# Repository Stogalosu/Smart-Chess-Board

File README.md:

# Smart Chess Board

## What?
A smart chess board that connects to your phone and automatically makes the moves you and your opponent make on the screen. It can even play against you! It works by moving a magnet under the board, thus also moving the pieces which will have magnets in them.

## Why?
Because I had this idea in the back if my head for a long time and I thought this was the perfect time. Also, I wanted a challenge, something new.

## How do I use it?
Well, I haven't thought it through, but my idea is to also make an Android app that connects through Bluetooth with the board so you can visualise the moves there, as well as make new ones. I also hope to allow players to make their own moves on the board using the Hall sensors that are in the board.

## Firmware
There is no firmware... yet. I've just finished assembling the board and will start working on the firmware soon. 

## Disclosure
This project has already been submitted to Blueprint a few months ago. In the meantime, I've made some small additions and adjustments that I've recorded using Lapse. These include:
- Adding pin holes on the x-axis idlers for the pulleys and then increasing their tolerances.
- Modifying X-carriage to avoid interference of belts with other moving pieces.
- Adding snap fit to every chess piece.
- Adding fillets to board edges.
- Reworking screw holes on the sides of the board.
- Strengthening the bottom of the board.
- Adjusting eject mechanism angle.
- Adjusting position of holes for Raspberry Pi.
- Adding holes in the bottom of the board for belt tensioning screws.
- Adding spaces for pin solders on the back of the PCB.
- Widening nut spaces in all pieces.
- Fixing nut holes for the motor holes; the nut was too close to the motor.
- Fixing small problems before shipping.

## Assembly
Print all pieces. Make sure to follow the color scheme of a real chess board and keep track of which piece is which, as some of the screw holes won't align if their positions are wrong. Slide together the 4 pieces that make up the bottom of the board while inserting the y-axis rods, the x-axis idlers and the x-axis guiderail. Screw in the motor holders and the motors. Cut your belt into 2 pieces. Slide them into the x-axis carriage and fit the belts on the pulleys as described in the following image. Screw in the x-axis carriage. Attach the servomotor.

Solder the pieces onto the PCB and solder them together by connecting the pins. Connect the botton pieces of the play surface with the little pins. Fit the PCBs into it, then screw in each wall piece while keeping track of its position. Connect the motor cables and the Raspberry Pi.

At the end, cover the bottom with the play surface and screw in all the screws. Done!

## Images
Build:

3D Render:

PCB that has the Raspberry Pi on it:

The other PCB, which will be used 3 times to form a grid:

Wiring diagrams for the special PCB:

Wiring diagram for tileable PCB:

## BOM table
|Name                          |Price/unit|Amount|Shipping|Product Cost|Notes           |Link                                                                                                        |
|------------------------------|----------|------|--------|------------|----------------|------------------------------------------------------------------------------------------------------------|
|X-axis guiderail              |$13,37    |1     |$0,00   |$13,37      |MGN9H, 350mm    |https://www.aliexpress.com/item/1005002516956172.html                                                       |
|Y-axis Steel Rod              |$2,21     |2     |$1,12   |$5,54       |6mm, 350mm      |https://www.aliexpress.com/item/1005007648646117.html                                                       |
|Y-axis Linear Bearing         |$1,26     |2     |$0,00   |$2,52       |LM6UU           |https://www.optimusdigital.ro/ro/mecanica-rulmenti/3812-rulment-liniar-lm6uu.html                           |
|Stepper Motor                 |$3,88     |2     |$0,00   |$7,76       |                |https://www.optimusdigital.ro/ro/motoare-motoare-pas-cu-pas/101-driver-uln2003-motor-pas-cu-pas-de-5-v-.html|
|Servomotor                    |$3,20     |1     |$0,00   |$3,20       |                |https://www.optimusdigital.ro/ro/motoare-servomotoare/26-micro-servomotor-sg90.html                         |
|Neodymium Magnet 6x3mm        |$2,26     |1     |$0,00   |$2,26       |                |https://www.emag.ro/magnet-neodim-disc-6mm-x-3mm-00004824/pd/DZW0Y6BBM/                                     |
|Neodymium Magnet 10x3mm       |$6,97     |2     |$6,48   |$20,42      |100pcs          |https://www.aliexpress.com/item/1005010439392352.html                                                       |
|GT2 Belt                      |$2,31     |1     |$1,82   |$4,13       |                |https://www.robofun.ro/3d-printer-cnc/curea-gt2-la-metru-liniar.html                                        |
|M3x6 Headless Screws          |$0,08     |10    |$0,00   |$0,77       |                |https://www.optimusdigital.ro/ro/mecanica-suruburi-si-piulite/5785-m3x6-mm-urub-de-fixare-cu-cap-plat.html  |
|M3x6 Screws                   |$0,02     |100   |$6,00   |$8,00       |Minimum quantity|https://www.tme.eu/ro/details/m3x6_d912-a2/suruburi-cu-piulita/kraftberg/                                   |
|M3x10 Screws                  |$0,03     |100   |$0,00   |$3,20       |Minimum quantity|https://www.tme.eu/ro/details/b3x10_bn3/suruburi-cu-piulita/bossard/1003771/                                |
|Steel Pins 2.5x10mm           |$4,60     |1     |$0,00   |$4,60       |50pcs           |https://www.aliexpress.com/item/1005003326358562.html                                                       |
|Steel Pins 4x30mm             |$5,04     |1     |$0,00   |$5,04       |20pcs           |https://www.aliexpress.com/item/1005003326358562.html                                                       |
|GT2 Timing Pulleys 5pcs       |$5,53     |1     |$2,99   |$8,52       |20T W6 B5       |https://www.aliexpress.com/item/1005001933418605.html                                                       |
|GT2 Idler Timing Pulleys 12pcs|$9,28     |2     |$2,99   |$21,55      |20T W6 B4       |https://www.aliexpress.com/item/1005007557987612.html                                                       |
|Hall Sensors                  |$0,41     |65    |$0,00   |$26,65      |                |https://www.tme.eu/ro/details/ss30at/senzori-hall/honeywell/                                                |
|I2C I/O expander              |$1,66     |1     |$0,00   |$1,66       |                |https://www.tme.eu/ro/en/details/tca9555pwr/interfaces-others-integrated-circuits/texas-instruments/        |
|I2C Driver                    |$1,69     |1     |$0,00   |$1,69       |                |https://www.tme.eu/ro/en/details/tbd62083afwg/drivers-integrated-circuits/toshiba/                          |
|Resistor network              |$0,30     |1     |$0,00   |$0,30       |                |https://www.tme.eu/ro/en/details/4609x-101-103lf/resistor-networks/bourns/                                  |
|Bus transciever               |$0,80     |1     |$0,00   |$0,80       |                |https://www.tme.eu/ro/en/details/sn74hct245dwr/latches/texas-instruments/                                   |
|Resistors                     |$0,03     |5     |$0,00   |$0,13       |                |https://www.tme.eu/ro/details/rc1206fr-072k7/rezistente-smd/yageo/rc1206fr-072k7l/                          |
|Inductors                     |$0,41     |4     |$0,00   |$1,64       |                |https://www.tme.eu/ro/details/b82422h1103k000/inductoare/epcos-tdk/                                         |
|Polarized Capacitors          |$0,70     |4     |$0,00   |$2,80       |                |https://www.tme.eu/ro/details/tajc107k010r/condensatoare-cu-tantal-smd/kyocera-avx/tajc107k010rnj/          |
|Capacitors                    |$0,17     |3     |$0,00   |$0,51       |                |https://www.tme.eu/ro/details/cl31b104kbcnnnd/condensatoare-mlcc-smd/samsung/                               |
|40 pin Connector Female       |$0,46     |1     |$0,00   |$0,46       |                |https://www.tme.eu/ro/details/zl262-40dg/pini-cu-benzi-si-soclu/connfly/ds1023-2-20s21/                     |
|40 pin Connector Male         |$4,51     |1     |$0,00   |$4,51       |                |https://www.tme.eu/ro/details/zl2038-40/pini-cu-benzi-si-soclu/ninigi/                                      |
|7 pin Connector Female        |$0,08     |10    |$0,00   |$0,81       |Minimum quantity|https://www.tme.eu/ro/details/zl262-7sg/pini-cu-benzi-si-soclu/connfly/ds1023-1-7s21/                       |
|4 pin Connector Female        |$0,08     |10    |$0,00   |$0,78       |Minimum quantity|https://www.tme.eu/ro/details/zl262-4sg/pini-cu-benzi-si-soclu/connfly/ds1023-1-4s21/                       |
|3 pin Connector Male          |$0,17     |1     |$0,00   |$0,17       |                |https://www.tme.eu/ro/details/tsw-103-07-l-s/pini-cu-benzi-si-soclu/samtec/                                 |
|PCBs                          |$29,40    |1     |$22,59  |$51,99      |                |                                                                                                            |
|Total Cost                    |          |      |$43,99  |$205,78     |                |                                                                                                            |

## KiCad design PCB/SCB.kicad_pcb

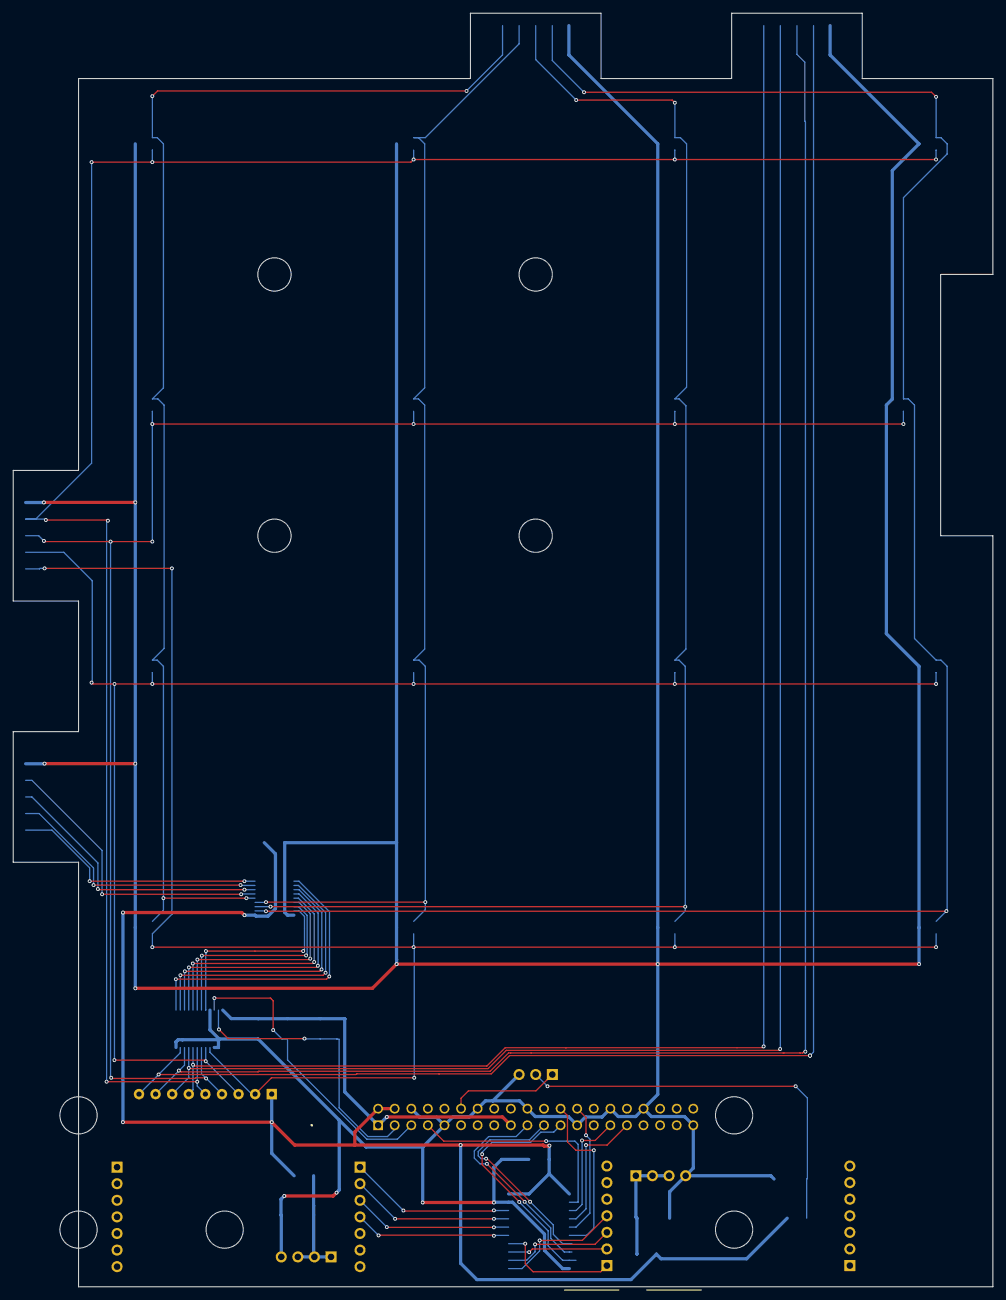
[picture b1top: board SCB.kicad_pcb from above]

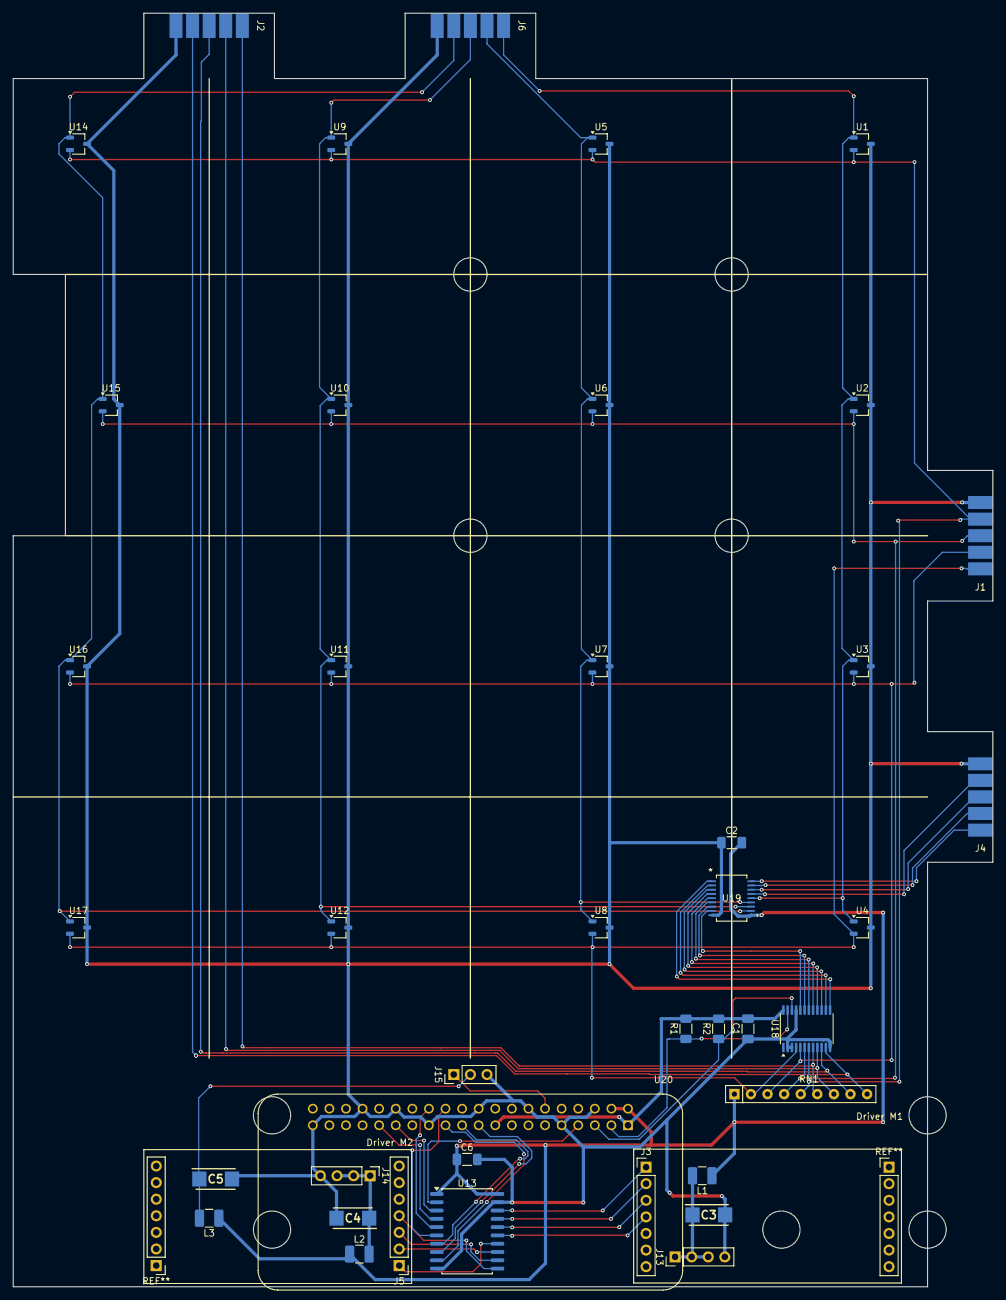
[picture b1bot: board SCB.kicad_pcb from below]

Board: 2 copper layers, 150.0 x 195.0 mm, 41 parts (40 on the bottom side), 49 nets.

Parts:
C1: C1; C_1206_3216Metric_Pad1.33x1.80mm_HandSolder
C2, C6: C; C_1206_3216Metric_Pad1.33x1.80mm_HandSolder
C3, C4, C5: C_Polarized; CAPPM6032X280N
J1, J2, J4, J6: Conn_01x05; Connector_5_Pads
J3, J5: Conn_01x07; PinHeader_1x07_P2.54mm_Vertical
J13, J14: Conn_01x04; PinHeader_1x04_P2.54mm_Vertical
J15: Conn_01x03; PinHeader_1x03_P2.54mm_Vertical
L1, L2, L3: L; L_1210_3225Metric_Pad1.42x2.65mm_HandSolder
R1, R2: R; R_1206_3216Metric_Pad1.30x1.75mm_HandSolder
RN1: R_Network08; R_Array_SIP9
U1, U2, U3, U4, U5, U6, U7, U8, U9, U10, U11, U12, U14, U15, U16, U17: TSOT-23
U13: SN74HCT245DWR; SOIC-20W_7.5x12.8mm_P1.27mm
U18: TCA9555PWR; TSSOP-24_4.4x7.8mm_P0.65mm
U19: TBD62083AFWG; SSOP18-P-225-0p65_TOS
U20: RASPBERRY_PI_ZERO_2_W; MODULE_RASPBERRY_PI_ZERO_2_W

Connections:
+3V3: C1.1, R1.2, R2.2, U18.24 (VCC), U20.1 (3V3_1), U20.17 (3V3_17)
+5V: C2.2, C6.1, L1.1, L2.1, L3.1, RN1.1 (common), U13.1 (A->B), U13.20 (VCC), U19.10 (COMMON), U20.2 (5V_2), U20.4 (5V_4)
/Matrice 4x4 cu controller/CA_IN: J4.1, U19.18 (O1)
/Matrice 4x4 cu controller/CB_IN: J4.2, U19.17 (O2)
/Matrice 4x4 cu controller/CC_IN: J4.3, U19.16 (O3)
/Matrice 4x4 cu controller/CD_IN: J4.4, U19.15 (O4)
/Matrice 4x4 cu controller/CE_IN: J6.1, U1.1 (VCC), U2.1 (VCC), U3.1 (VCC), U4.1 (VCC), U19.14 (O5)
/Matrice 4x4 cu controller/CF_IN: J6.2, U5.1 (VCC), U6.1 (VCC), U7.1 (VCC), U8.1 (VCC), U19.13 (O6)
/Matrice 4x4 cu controller/CG_IN: J6.3, U9.1 (VCC), U10.1 (VCC), U11.1 (VCC), U12.1 (VCC), U19.12 (O7)
/Matrice 4x4 cu controller/CH_IN: J6.4, U14.1 (VCC), U15.1 (VCC), U16.1 (VCC), U17.1 (VCC), U19.11 (O8)
/Matrice 4x4 cu controller/L1_IN: J1.1, RN1.2 (R1), U4.2 (OUT), U8.2 (OUT), U12.2 (OUT), U17.2 (OUT), U18.4 (P00)
/Matrice 4x4 cu controller/L2_IN: J1.2, RN1.3 (R2), U3.2 (OUT), U7.2 (OUT), U11.2 (OUT), U16.2 (OUT), U18.5 (P01)
/Matrice 4x4 cu controller/L3_IN: J1.3, RN1.4 (R3), U2.2 (OUT), U6.2 (OUT), U10.2 (OUT), U15.2 (OUT), U18.6 (P02)
/Matrice 4x4 cu controller/L4_IN: J1.4, RN1.5 (R4), U1.2 (OUT), U5.2 (OUT), U9.2 (OUT), U14.2 (OUT), U18.7 (P03)
/Matrice 4x4 cu controller/L5_OUT: J2.1, RN1.6 (R5), U18.8 (P04)
/Matrice 4x4 cu controller/L6_OUT: J2.2, RN1.7 (R6), U18.9 (P05)
/Matrice 4x4 cu controller/L7_OUT: J2.3, RN1.8 (R7), U18.10 (P06)
/Matrice 4x4 cu controller/L8_OUT: J2.4, RN1.9 (R8), U18.11 (P07)
/Raspberry/IO_4: U13.2 (A0), U20.7 (GPIO4/GPIO_GCLK)
/Raspberry/IO_5: U13.3 (A1), U20.29 (GPIO5)
/Raspberry/IO_6: U13.4 (A2), U20.31 (GPIO6)
/Raspberry/IO_7: U13.5 (A3), U20.26 (GPIO7/SPI_~CE1)
/Raspberry/IO_8: U13.6 (A4), U20.24 (GPIO8/SPI_~CE0)
/Raspberry/IO_9: U13.7 (A5), U20.21 (GPIO9/SPI_MISO)
/Raspberry/IO_10: U13.8 (A6), U20.19 (GPIO10/SPI_MOSI)
/Raspberry/IO_11: U13.9 (A7), U20.23 (GPIO11/SPI_SCLK)
/Raspberry/M1_1: J3.1, U13.18 (B0)
/Raspberry/M1_2: J3.2, U13.17 (B1)
/Raspberry/M1_3: J3.3, U13.16 (B2)
/Raspberry/M1_4: J3.4, U13.15 (B3)
/Raspberry/M2_1: J5.1, U13.14 (B4)
/Raspberry/M2_2: J5.2, U13.13 (B5)
/Raspberry/M2_3: J5.3, U13.12 (B6)
/Raspberry/M2_4: J5.4, U13.11 (B7)
/Raspberry/MZ: J15.1, U20.12 (GPIO18/GPIO_GEN1)
GND: C1.2, C2.1, C3.2, C4.2, C5.2, C6.2, J1.5, J2.5, J4.5, J6.5, J13.4, J14.4, J15.3, U1.3 (GND), U2.3 (GND), U3.3 (GND), U4.3 (GND), U5.3 (GND), U6.3 (GND), U7.3 (GND), U8.3 (GND), U9.3 (GND), U10.3 (GND), U11.3 (GND), U12.3 (GND), U13.10 (GND), U13.19 (CE), U14.3 (GND), U15.3 (GND), U16.3 (GND), U17.3 (GND), U18.2 (A1), U18.3 (A2), U18.12 (GND), U18.21 (A0), U19.9 (GND), U20.6 (GND_6), U20.9 (GND_9), U20.14 (GND_14), U20.20 (GND_20), U20.25 (GND_25), U20.30 (GND_30), U20.34 (GND_34), U20.39 (GND_39)
unnamed: C3.1, J13.1, J13.2, J13.3, L1.2
unnamed: C4.1, J14.1, J14.2, J14.3, L2.2
unnamed: C5.1, J15.2, L3.2
unnamed: U18.13 (P10), U19.1 (I1)
unnamed: U18.14 (P11), U19.2 (I2)
unnamed: U18.15 (P12), U19.3 (I3)
unnamed: U18.16 (P13), U19.4 (I4)
unnamed: U18.17 (P14), U19.5 (I5)
unnamed: U18.18 (P15), U19.6 (I6)
unnamed: U18.19 (P16), U19.7 (I7)
unnamed: U18.20 (P17), U19.8 (I8)
SCL: R2.1, U18.22 (SCL), U20.5 (GPIO3/SCL)
SDA: R1.1, U18.23 (SDA), U20.3 (GPIO2/SDA1)

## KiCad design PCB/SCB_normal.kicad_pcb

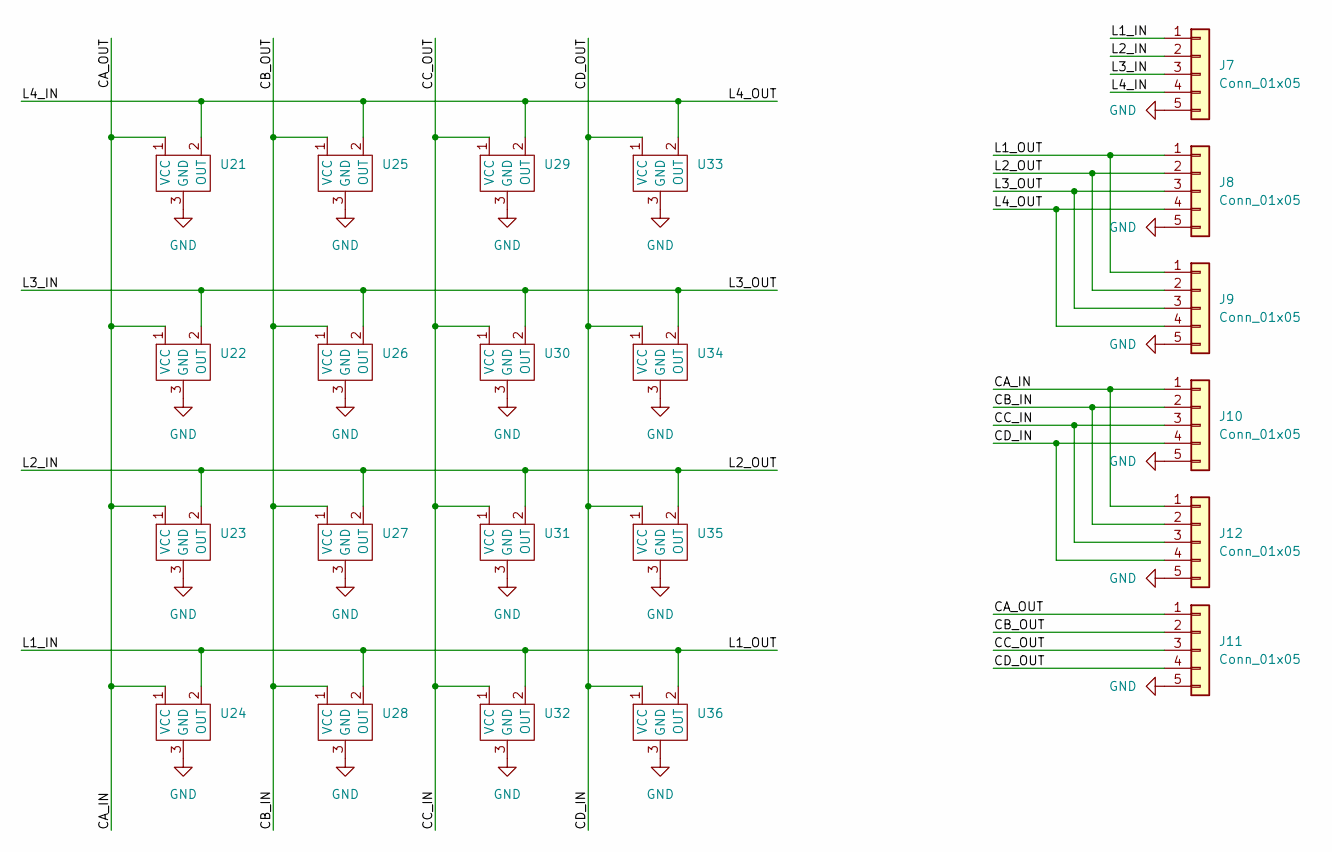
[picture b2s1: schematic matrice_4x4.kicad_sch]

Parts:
J7, J8, J9, J10, J11, J12: Conn_01x05; Connector_5_Pads
U21, U22, U23, U24, U25, U26, U27, U28, U29, U30, U31, U32, U33, U34, U35, U36: TSOT-23

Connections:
/Matrice 4x4/CA_IN: J10.1, J11.1, J12.1, U21.1 (VCC), U22.1 (VCC), U23.1 (VCC), U24.1 (VCC)
/Matrice 4x4/CB_IN: J10.2, J11.2, J12.2, U25.1 (VCC), U26.1 (VCC), U27.1 (VCC), U28.1 (VCC)
/Matrice 4x4/CC_IN: J10.3, J11.3, J12.3, U29.1 (VCC), U30.1 (VCC), U31.1 (VCC), U32.1 (VCC)
/Matrice 4x4/CD_IN: J10.4, J11.4, J12.4, U33.1 (VCC), U34.1 (VCC), U35.1 (VCC), U36.1 (VCC)
/Matrice 4x4/L1_IN: J7.1, J8.1, J9.1, U24.2 (OUT), U28.2 (OUT), U32.2 (OUT), U36.2 (OUT)
/Matrice 4x4/L2_IN: J7.2, J8.2, J9.2, U23.2 (OUT), U27.2 (OUT), U31.2 (OUT), U35.2 (OUT)
/Matrice 4x4/L3_IN: J7.3, J8.3, J9.3, U22.2 (OUT), U26.2 (OUT), U30.2 (OUT), U34.2 (OUT)
/Matrice 4x4/L4_IN: J7.4, J8.4, J9.4, U21.2 (OUT), U25.2 (OUT), U29.2 (OUT), U33.2 (OUT)
GND: J7.5, J8.5, J9.5, J10.5, J11.5, J12.5, U21.3 (GND), U22.3 (GND), U23.3 (GND), U24.3 (GND), U25.3 (GND), U26.3 (GND), U27.3 (GND), U28.3 (GND), U29.3 (GND), U30.3 (GND), U31.3 (GND), U32.3 (GND), U33.3 (GND), U34.3 (GND), U35.3 (GND), U36.3 (GND)

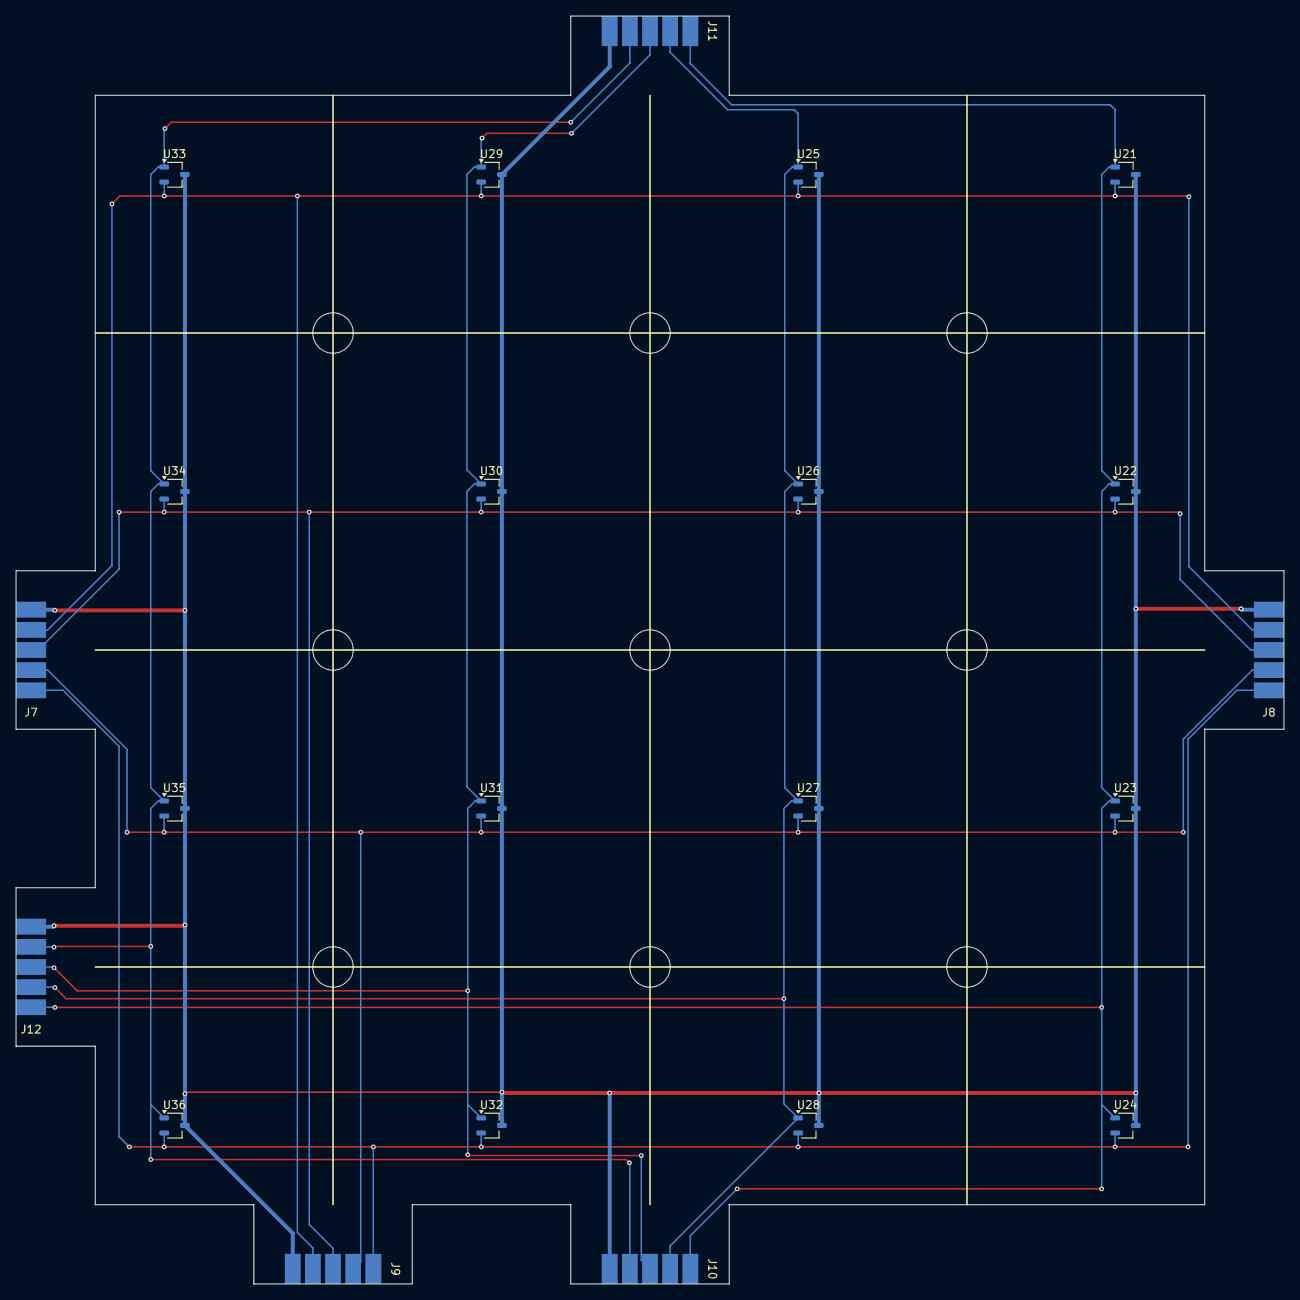
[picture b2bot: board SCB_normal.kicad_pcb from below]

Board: 2 copper layers, 160.0 x 160.0 mm, 22 parts (22 on the bottom side), 9 nets.

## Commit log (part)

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2026-01-29 Enhance README with project details and BOM
    Expanded README to include detailed project description, usage instructions, images, and BOM table.
2026-01-30 Uploaded all project files
2026-01-30 Updated prices in BOM
2026-02-04 Fixed holes in the PCBs
2026-06-28 Update README with build
